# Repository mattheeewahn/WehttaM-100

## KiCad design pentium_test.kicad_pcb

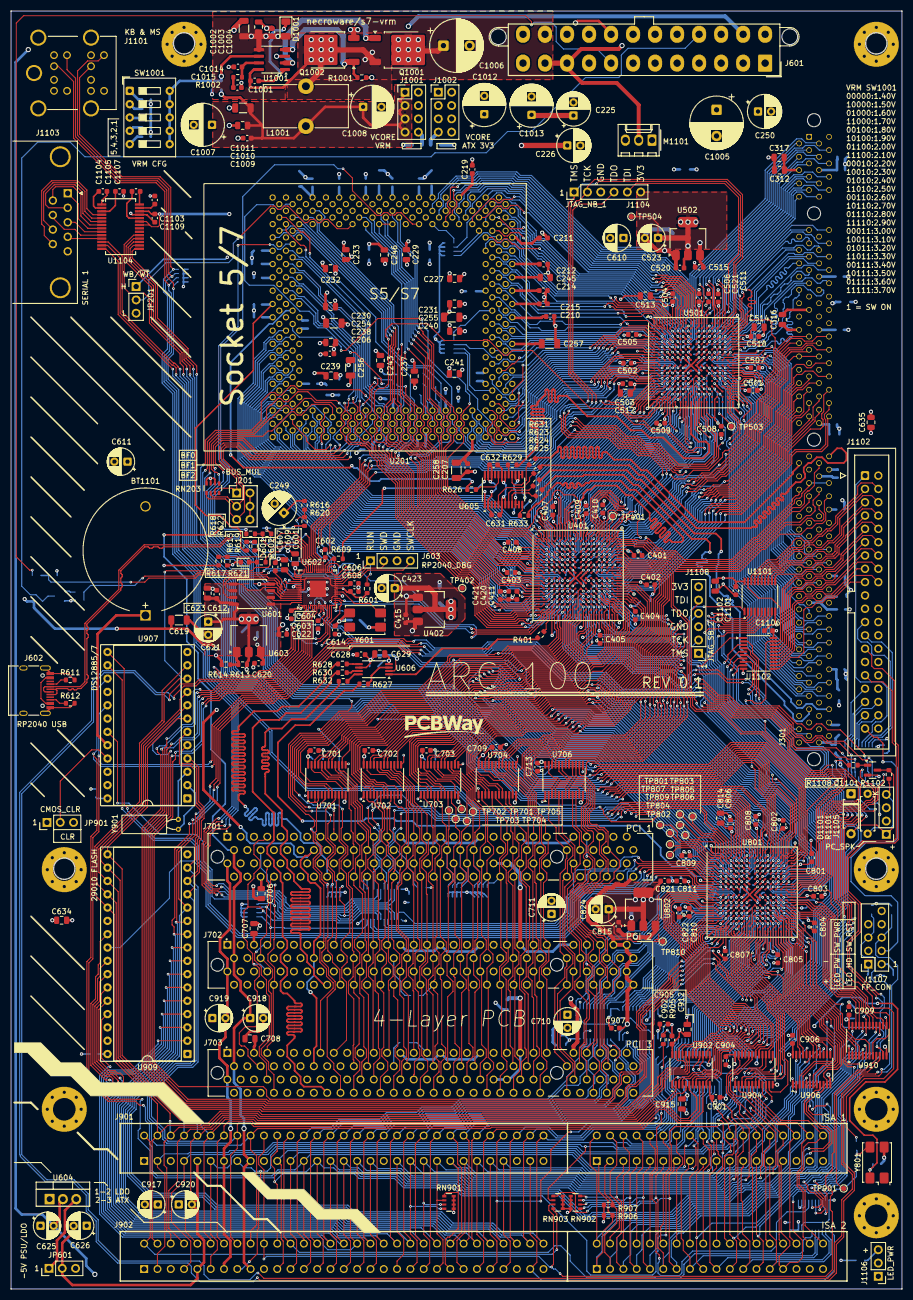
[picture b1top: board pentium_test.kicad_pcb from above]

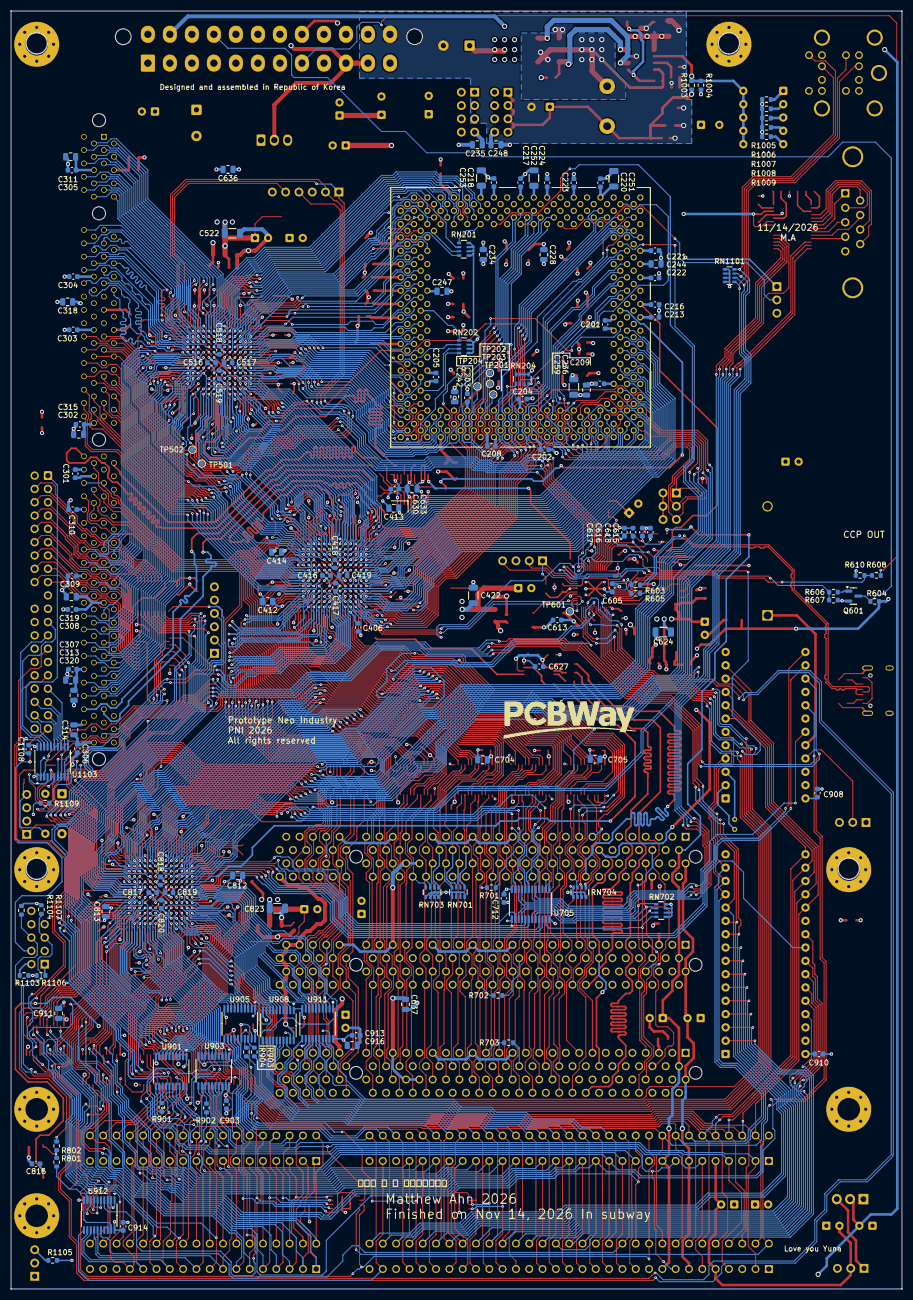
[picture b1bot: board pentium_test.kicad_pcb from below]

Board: 4 copper layers, 170.0 x 243.8 mm, 425 parts (143 on the bottom side), 774 nets.

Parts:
BT1101: Battery_Cell; BatteryHolder_MYOUNG_BS-07-A1BJ001_CR2032
C201, C202, C203, C204, C205, C206, C207, C208, C209, C210, C211, C212, C213, C214, C215, C216, C217, C218, C219, C220, C221, C222, C223, C224, C301, C302, C303, C304, C305, C306, C307, C308, C309, C310, C401, C402, C403, C404, C405, C406, C407, C408, C409, C410, C411, C415, C416, C417, C418, C419, C501, C502, C503, C504, C505, C506, C507, C508, C509, C510, C511, C515, C516, C517, C518, C519, C602, C603, C604, C605, C606, C607, C608, C612, C614, C615, C616, C617, C618, C620, C622, C627, C628, C630, C631, C632, C701, C702, C703, C709, C712, C713, C801, C802, C803, C804, C805, C806, C807, C808, C809, C810, C811, C815, C816, C817, C818, C819, C820, C901, C902, C903, C904, C905, C906, C907, C908, C909, C910, C913, C914, C1001, C1004, C1009, C1101, C1103, C1104, C1105, C1106, C1107, C1108, C1109: 100n; C_0603_1608Metric
C225, C226, C249, C250: 220u; CP_Radial_D6.3mm_P2.50mm
C227, C228, C229, C230, C231, C232, C233, C234, C235, C236, C237, C238, C239, C240, C241, C242, C243, C311, C312, C313, C314, C315, C316, C412, C413, C414, C512, C513, C514, C601, C609, C623, C629, C633, C634, C635, C636, C637, C704, C705, C706, C707, C708, C812, C813, C814, C911, C912, C915, C916, C1102: 1u; C_0805_2012Metric
C244, C245, C246, C247, C248, C317, C318, C319, C320, C1003, C1010: 4.7u; C_0805_2012Metric
C251, C252, C253, C254, C255, C422, C522, C619, C624, C823: 22u; C_1206_3216Metric
C256, C257, C258, C259, C1002, C1011: 10u; C_1206_3216Metric
C420, C421, C520, C521, C613, C821, C822: 4.7u; C_0603_1608Metric
C423, C523, C610, C611, C621, C710, C711, C824, C917, C918, C919, C920: 47u; CP_Radial_D5.0mm_P2.50mm
C625, C626: 22u; CP_Radial_D5.0mm_P2.50mm
C1005, C1006: 2200u; CP_Radial_D10.0mm_P5.00mm
C1007, C1008, C1012, C1013: 1000u; CP_Radial_D8.0mm_P3.50mm
C1014: 39p; C_0603_1608Metric
C1015: 242n; C_0603_1608Metric
D601: LED; LED_0603_1608Metric
D1001: D; D_1206_3216Metric
D1101: 1N4148; D_A-405_P7.62mm_Horizontal
H101, H102, H103, H104, H105, H106, H107: MountingHole_Pad; MountingHole_4.3mm_M4_Pad_Via
J201: Bus speed; PinHeader_2x03_P2.54mm_Vertical
J301: sdram
J601: ATX-24; Molex_Mini-Fit_Jr_5566-24A2_2x12_P4.20mm_Vertical
J602: USB_C_Receptacle_USB2.0_16P; USB_C_Receptacle_HRO_TYPE-C-31-M-12
J603: RP2040_DEBUG; PinHeader_1x04_P2.54mm_Vertical
J701, J702, J703: PCI 5V 32-bit; TE_1-5145154-2
J901, J902: TE_7-5530843-0
J1001, J1002: Conn_02x04_Odd_Even; PinHeader_2x04_P2.54mm_Vertical
J1101: MH11061-D2_kb_ms_combo
J1102: idc_02x20_IDE
J1103: RS232; DSUB-9_Pins_Horizontal_P2.77x2.84mm_EdgePinOffset7.70mm_Hou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
J1104: FPGA_JTAG1; PinHeader_1x06_P2.54mm_Vertical
J1105: PC_SPK; PinHeader_1x04_P2.54mm_Vertical
J1106: PWR_LED; PinHeader_1x03_P2.54mm_Vertical
J1107: front_panel_2x05
J1108: FPGA_JTAG2; PinHeader_1x06_P2.54mm_Vertical
JP201, JP601: Jumper_3_Open; PinHeader_1x03_P2.54mm_Vertical
JP901: CMOS_CLR; PinHeader_1x03_P2.54mm_Vertical
L1001: 3.3u; L_Toroid_Vertical_L16.0mm_W8.0mm_P7.62mm
M1101: Fan_PC_Chassis; Molex_KK-254_AE-6410-03A_1x03_P2.54mm_Vertical
Q601, Q1101: BSS138; SOT-23
Q1001, Q1002: Q_NMOS_GDS SM480T9RL; TO-252-2
R401, R609, R623, R624, R625, R626, R627, R628, R629, R630, R631, R632, R633, R801, R802, R901, R902, R903, R904, R905: 33; R_0603_1608Metric
R601, R602, R1102, R1103, R1105, R1106: 1K; R_0603_1608Metric
R603, R605: 27; R_0603_1608Metric
R604, R607, R616, R617, R622: 10K; R_0603_1608Metric
R606, R701, R702, R703, R1108: 100; R_0603_1608Metric
R608: 1.8K; R_0603_1608Metric
R610: 3.3K; R_0603_1608Metric
R611, R612: 5.1K; R_0603_1608Metric
R613: 120; R_0603_1608Metric
R614: 200; R_0603_1608Metric
R615, R1104, R1107, R1109: 4.7K; R_0603_1608Metric
R618, R620: 33K; R_0603_1608Metric
R619: 47K; R_0603_1608Metric
R621, R1001, R1002, R1006: 15K; R_0603_1608Metric
R906, R907: 300; R_0603_1608Metric
R1003: 5K; R_0603_1608Metric
R1004, R1008, R1009: 3.75K; R_0603_1608Metric
R1005: 30K; R_0603_1608Metric
R1007: 7.5K; R_0603_1608Metric
R1101: 47; R_Axial_DIN0207_L6.3mm_D2.5mm_P7.62mm_Horizontal
RN201, RN202, RN203, RN204, RN701, RN702, RN703, RN704, RN1101: 4.7K; R_Array_Convex_4x0603
RN901, RN902, RN903: 1K; R_Array_Convex_4x0603
SW1001: SW_DIP_x05; SW_DIP_SPSTx05_Slide_9.78x14.88mm_W7.62mm_P2.54mm
TP201: CPU_TMS; TestPoint_Pad_D1.0mm
TP202: CPU_TDO; TestPoint_Pad_D1.0mm
TP203: CPU_TDI; TestPoint_Pad_D1.0mm
TP204: CPU_TCK; TestPoint_Pad_D1.0mm
TP401, TP901: TestPoint; TestPoint_Pad_D1.0mm
TP402: CTRL_VCCINT; TestPoint_Pad_D1.0mm
TP501: FPGA_DATA_SPARE1; TestPoint_Pad_D1.0mm
TP502: FPGA_DATA_SPARE2; TestPoint_Pad_D1.0mm
TP503: FPGA_DATA_SPARE3; TestPoint_Pad_D1.0mm
TP504: DATA_VCCINT; TestPoint_Pad_D1.0mm
TP601: RP_GPIO12; TestPoint_Pad_D1.0mm
TP701: PCI_GND; TestPoint_Pad_D1.0mm
TP702: PCI5_FRAME; TestPoint_Pad_D1.0mm
TP703: PCI5_IRDY; TestPoint_Pad_D1.0mm
TP704: PCI5_TRDY; TestPoint_Pad_D1.0mm
TP705: PCI5_DEVSEL; TestPoint_Pad_D1.0mm
TP801: FPGA_ISA_SPARE1; TestPoint_Pad_D1.0mm
TP802: FPGA_ISA_SPARE6; TestPoint_Pad_D1.0mm
TP803: FPGA_ISA_SPARE2; TestPoint_Pad_D1.0mm
TP804: FPGA_ISA_SPARE7; TestPoint_Pad_D1.0mm
TP805: FPGA_ISA_SPARE3; TestPoint_Pad_D1.0mm
TP806: FPGA_ISA_SPARE8; TestPoint_Pad_D1.0mm
TP807: FPGA_ISA_SPARE4; TestPoint_Pad_D1.0mm
TP809: FPGA_ISA_SPARE5; TestPoint_Pad_D1.0mm
TP810: ISA_VCCINT; TestPoint_Pad_D1.0mm
U201: PGA321; PGA-321
U401, U501, U801: XC6SLX9-FTG256; Xilinx_FTG256
U402, U502, U802: LDL1117S12R; SOT-223-3_TabPin2
U601: W25Q128JVS; SOIC-8_5.3x5.3mm_P1.27mm
U602: RP2040; QFN-56-1EP_7x7mm_P0.4mm_EP3.2x3.2mm
U603: AMS1117; SOT-223-3_TabPin2
U604: LM7905_TO220; TO-220-3_Vertical
U605: CDCVF2310PW; TSSOP-24_4.4x7.8mm_P0.65mm
U606: CDCV304; TSSOP-8_4.4x3mm_P0.65mm
U701, U702, U703, U704, U705, U706, U902, U904, U906, U910: 74CBTD3384APW; TSSOP-24_4.4x7.8mm_P0.65mm
U901, U903, U905, U908, U911, U912, U1103: 74HCT541; TSSOP-20_4.4x6.5mm_P0.65mm
U907: DIP-24_W15.24mm_Socket
U909: SST39SF010; DIP-32_W15.24mm_Socket
U1001: ISL6545; SOIC-8_3.9x4.9mm_P1.27mm
U1101, U1102: SN74LVC245APW; TSSOP-20_4.4x6.5mm_P0.65mm
U1104: MAX3243E; SSOP-28_5.3x10.2mm_P0.65mm
Y601: 12 MHz; Crystal_SMD_7050-4Pin_7.0x5.0mm
Y801: 14.318 MHz; Crystal_SMD_7050-4Pin_7.0x5.0mm
Y901: 32.768 KHz; Crystal_C38-LF_D3.0mm_L8.0mm_Horizontal

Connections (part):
+1V2_F1: C416.1, C417.1, C418.1, C419.1, C420.1, C421.1, C422.1, C423.1, TP402.1, U401.G7 (VCCINT), U401.G9 (VCCINT), U401.H8 (VCCINT), U401.H10 (VCCINT), U401.J7 (VCCINT), U401.J9 (VCCINT), U401.K8 (VCCINT), U401.K10 (VCCINT), U402.2 (VO)
+1V2_F2: C516.1, C517.1, C518.1, C519.1, C520.1, C521.1, C522.1, C523.1, TP504.1, U501.G7 (VCCINT), U501.G9 (VCCINT), U501.H8 (VCCINT), U501.H10 (VCCINT), U501.J7 (VCCINT), U501.J9 (VCCINT), U501.K8 (VCCINT), U501.K10 (VCCINT), U502.2 (VO)
+1V2_F3: C817.1, C818.1, C819.1, C820.1, C821.1, C822.1, C823.1, C824.1, TP810.1, U801.G7 (VCCINT), U801.G9 (VCCINT), U801.H8 (VCCINT), U801.H10 (VCCINT), U801.J7 (VCCINT), U801.J9 (VCCINT), U801.K8 (VCCINT), U801.K10 (VCCINT), U802.2 (VO)
+3V3: C201.1, C202.1, C203.1, C204.1, C205.1, C206.1, C207.1, C208.1, C209.1, C210.1, C236.1, C237.1, C238.1, C239.1, C240.1, C241.1, C242.1, C243.1, C249.1, C250.1, C256.1, C257.1, C258.1, C259.1, C301.1, C302.1, C303.1, C304.1, C305.1, C306.1, C307.1, C308.1, C309.1, C310.1, C311.1, C312.1, C313.1, C314.1, C315.1, C316.1, C317.1, C318.1, C319.1, C320.1, C401.1, C402.1, C403.1, C404.1, C405.1, C406.1, C407.1, C408.1, C409.1, C410.1, C411.1, C412.1, C413.1, C414.1, C415.1, C501.1, C502.1, C503.1, C504.1, C505.1, C506.1, C507.1, C508.1, C509.1, C510.1, C511.1, C512.1, C513.1, C514.1, C515.1, C610.1, C627.1, C628.1, C629.1, C630.1, C631.1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
+3V3SB: C601.1, C602.1, C603.1, C604.1, C605.1, C606.1, C612.1, C613.1, C614.1, C621.1, C622.1, C623.1, C624.1, J701.A14 (3.3V_AUX), J702.A14 (3.3V_AUX), J703.A14 (3.3V_AUX), R601.1, R613.1, U601.8 (VCC), U602.1 (IOVDD), U602.10 (IOVDD), U602.22 (IOVDD), U602.33 (IOVDD), U602.42 (IOVDD), U602.43 (ADC_AVDD), U602.44 (VREG_IN), U602.48 (USB_VDD), U602.49 (IOVDD), U603.2 (VO), Y601.4 (Vdd)
+5V: C611.1, C634.1, C635.1, C701.1, C702.1, C703.1, C704.1, C705.1, C706.1, C707.1, C708.1, C709.1, C710.1, C712.1, C713.1, C901.2, C902.1, C903.2, C904.1, C905.2, C906.1, C907.2, C908.2, C909.1, C910.2, C911.1, C912.1, C913.2, C914.2, C915.1, C916.1, C917.1, C1002.1, C1003.1, C1004.1, C1005.1, C1006.1, C1108.2, D1001.2 (A), D1101.1 (K), J601.4 (+5V), J601.6 (+5V), J601.21 (+5V), J601.22 (+5V), J601.23 (+5V), J701.A5 (+5V), J701.A8 (+5V), J701.A10 (IOPWR), J701.A16 (IOPWR), J701.A59 (IOPWR), J701.A61 (+5V), J701.A62 (+5V), J701.B5 (+5V), J701.B6 (+5V), J701.B19 (IOPWR), J701.B59 (IOPWR), J701.B61 (+5V), J701.B62 (+5V), J702.A5 (+5V), J702.A8 (+5V), J702.A10 (IOPWR), J702.A16 (IOPWR), J702.A59 (IOPWR), J702.A61 (+5V), J702.A62 (+5V), J702.B5 (+5V), J702.B6 (+5V), J702.B19 (IOPWR), J702.B59 (IOPWR), J702.B61 (+5V), J702.B62 (+5V), J703.A5 (+5V), J703.A8 (+5V), J703.A10 (IOPWR), J703.A16 (IOPWR), J703.A59 (IOPWR), J703.A61 (+5V), J703.A62 (+5V), J703.B5 (+5V), J703.B6 (+5V)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
+5VSB: C619.1, C620.1, J601.9 (+5VSB), R604.1, U603.3 (VI)
+12V: C918.1, J601.10 (+12V), J601.11 (+12V), J701.A2 (+12V), J702.A2 (+12V), J703.A2 (+12V), J901.B9 (+12V), J902.B9 (+12V), M1101.2 (+), R618.1
+BATT: BT1101.1 (+), U907.20 (VBAT)
-5V: C626.2, C920.2, J901.B5 (-5V), J902.B5 (-5V), JP601.2 (C)
-5V_ATX: J601.20 (-5V), JP601.3 (B)
-12V: C625.2, C919.2, J601.14 (-12V), J701.B1 (-12V), J702.B1 (-12V), J703.B1 (-12V), J901.B7 (-12V), J902.B7 (-12V), U604.2 (VI)
/IO/IDE5_D0: J1102.17 (D0), U1102.11 (B8)
/IO/IDE5_D1: J1102.15 (D1), U1102.13 (B6)
/IO/IDE5_D2: J1102.13 (D2), U1102.15 (B4)
/IO/IDE5_D3: J1102.11 (D3), U1102.17 (B2)
/IO/IDE5_D4: J1102.9 (D4), U1101.11 (B8)
/IO/IDE5_D5: J1102.7 (D5), U1101.13 (B6)
/IO/IDE5_D6: J1102.5 (D6), U1101.15 (B4)
/IO/IDE5_D7: J1102.3 (D7), U1101.17 (B2)
/IO/IDE5_D8: J1102.4 (D8), U1101.18 (B1)
/IO/IDE5_D9: J1102.6 (D9), U1101.16 (B3)
/IO/IDE5_D10: J1102.8 (D10), U1101.14 (B5)
/IO/IDE5_D11: J1102.10 (D11), U1101.12 (B7)
/IO/IDE5_D12: J1102.12 (D12), U1102.18 (B1)
/IO/IDE5_D13: J1102.14 (D13), U1102.16 (B3)
/IO/IDE5_D14: J1102.16 (D14), U1102.14 (B5)
/IO/IDE5_D15: J1102.18 (D15), U1102.12 (B7)
/IO/IDE5_DASP: J1102.39 (~DASP), J1107.3
/IO/IDE_BUF_DA0: J1102.35 (DA0), U1103.12 (Y6)
/IO/IDE_BUF_DA1: J1102.33 (DA1), U1103.11 (Y7)
/IO/IDE_BUF_DA2: J1102.36 (DA2), U1103.13 (Y5)
/IO/RS232_1_CTS: J1103.8, U1104.5 (RIN2)
/IO/RS232_1_DCD: J1103.1, U1104.8 (RIN5)
/IO/RS232_1_DSR: J1103.6, U1104.7 (RIN4)
/IO/RS232_1_DTR: J1103.4, U1104.11 (DOUT3)
/IO/RS232_1_RI: J1103.9, U1104.4 (RIN1)
/IO/RS232_1_RTS: J1103.7, U1104.10 (DOUT2)
/IO/RS232_1_RXD: J1103.2, U1104.6 (RIN3)
/IO/RS232_1_TXD: J1103.3, U1104.9 (DOUT1)
/IO/~IDE_BUF_CS1FX: J1102.37 (~CS1FX), U1103.14 (Y4)
/IO/~IDE_BUF_CS3FX: J1102.38 (~CS3FX), U1103.15 (Y3)
/IO/~IDE_BUF_DIOR: J1102.25 (~DIOR), U1103.18 (Y0)
/IO/~IDE_BUF_DIOW: J1102.23 (~DIOW), U1103.17 (Y1)
/IO/~IDE_BUF_RESET: J1102.1 (~RESET), U1103.16 (Y2)
/ISA/ISA5_AEN: J901.A11 (AEN), J902.A11 (AEN), U901.11 (Y7)
/ISA/ISA5_ALE: J901.B28 (ALE), J902.B28 (ALE), U903.11 (Y7)
/ISA/ISA5_CLK: J901.B20 (CLK), J902.B20 (CLK), U901.15 (Y3)
/ISA/ISA5_DRQ0: J901.D9 (DRQ0), J902.D9 (DRQ0), U910.5 (1B2)
/ISA/ISA5_DRQ1: J901.B18 (DRQ1), J902.B18 (DRQ1), U906.16 (2B2)
/ISA/ISA5_DRQ2: J901.B6 (DRQ2), J902.B6 (DRQ2), U904.15 (2B1)
/ISA/ISA5_DRQ3: J901.B16 (DRQ3), J902.B16 (DRQ3), U906.5 (1B2)
/ISA/ISA5_DRQ5: J901.D11 (DRQ5), J902.D11 (DRQ5), U910.6 (1B3)
/ISA/ISA5_DRQ6: J901.D13 (DRQ6), J902.D13 (DRQ6), U910.16 (2B2)
/ISA/ISA5_DRQ7: J901.D15 (DRQ7), J902.D15 (DRQ7), U910.15 (2B1)
/ISA/ISA5_IRQ2: J901.B4 (IRQ2), J902.B4 (IRQ2), RN903.2 (R2.1), U904.16 (2B2)
/ISA/ISA5_IRQ3: J901.B25 (IRQ3), J902.B25 (IRQ3), U904.10 (1B5)
/ISA/ISA5_IRQ4: J901.B24 (IRQ4), J902.B24 (IRQ4), RN901.1 (R1.1), U906.23 (2B5)
/ISA/ISA5_IRQ5: J901.B23 (IRQ5), J902.B23 (IRQ5), RN901.2 (R2.1), U906.20 (2B4)
/ISA/ISA5_IRQ6: J901.B22 (IRQ6), J902.B22 (IRQ6), RN901.3 (R3.1), U906.2 (1B1)
/ISA/ISA5_IRQ7: J901.B21 (IRQ7), J902.B21 (IRQ7), RN901.4 (R4.1), U906.19 (2B3)
/ISA/ISA5_IRQ10: J901.D3 (IRQ10), J902.D3 (IRQ10), RN902.4 (R4.1), U906.10 (1B5)
/ISA/ISA5_IRQ11: J901.D4 (IRQ11), J902.D4 (IRQ11), RN902.3 (R3.1), U910.23 (2B5)
/ISA/ISA5_IRQ12: J901.D5 (IRQ12), J902.D5 (IRQ12), RN902.2 (R2.1), U910.2 (1B1)
/ISA/ISA5_IRQ15: J901.D6 (IRQ15), J902.D6 (IRQ15), RN902.1 (R1.1), U910.20 (2B4)
/ISA/ISA5_LA17: J901.C8 (LA17), J902.C8 (LA17), U903.16 (Y2)
/ISA/ISA5_LA18: J901.C7 (LA18), J902.C7 (LA18), U905.11 (Y7)
/ISA/ISA5_LA19: J901.C6 (LA19), J902.C6 (LA19), U905.14 (Y4)
/ISA/ISA5_LA20: J901.C5 (LA20), J902.C5 (LA20), U905.15 (Y3)
/ISA/ISA5_LA21: J901.C4 (LA21), J902.C4 (LA21), U905.13 (Y5)
/ISA/ISA5_LA22: J901.C3 (LA22), J902.C3 (LA22), U905.12 (Y6)
/ISA/ISA5_LA23: J901.C2 (LA23), J902.C2 (LA23), U903.18 (Y0)
/ISA/ISA5_OSC: J901.B30 (OSC), J902.B30 (OSC), U912.11 (Y7)
/ISA/ISA5_RESET: J901.B2 (RESET), J902.B2 (RESET), U903.17 (Y1)
/ISA/ISA5_SBHE: J901.C1 (SBHE), J902.C1 (SBHE), U906.6 (1B3)
/ISA/ISA5_TC: J901.B27 (TC), J902.B27 (TC), U901.17 (Y1)
/ISA/SB_SPARE5_1: TP901.1, U910.10 (1B5)
/ISA/~CMOS_CLR: JP901.2 (C), U907.21 (~RCLR)
/ISA/~ISA5_DACK0: J901.D8 (~DACK0), J902.D8 (~DACK0), U912.15 (Y3)
/ISA/~ISA5_DACK1: J901.B17 (~DACK1), J902.B17 (~DACK1), U901.14 (Y4)
/ISA/~ISA5_DACK2: J901.B26 (~DACK2), J902.B26 (~DACK2), U901.16 (Y2)
/ISA/~ISA5_DACK3: J901.B15 (~DACK3), J902.B15 (~DACK3), U901.13 (Y5)
/ISA/~ISA5_DACK5: J901.D10 (~DACK5), J902.D10 (~DACK5), U912.14 (Y4)
/ISA/~ISA5_DACK6: J901.D12 (~DACK6), J902.D12 (~DACK6), U912.13 (Y5)
/ISA/~ISA5_DACK7: J901.D14 (~DACK7), J902.D14 (~DACK7), U912.12 (Y6)
/ISA/~ISA5_IOCHECK: J901.A1 (IO), J902.A1 (IO), RN903.4 (R4.1)
/ISA/~ISA5_IOCS16: J901.D2 (~IOCS16), J902.D2 (~IOCS16), R907.1, U906.9 (1B4)
/ISA/~ISA5_MEMCS16: J901.D1 (~MEMCS16), J902.D1 (~MEMCS16), R906.1, U906.15 (2B1)
/ISA/~ISA5_MEMR: J901.C9 (~MEMR), J902.C9 (~MEMR), U903.13 (Y5)
/ISA/~ISA5_MEMW: J901.C10 (~MEMW), J902.C10 (~MEMW), U901.18 (Y0)
/ISA/~ISA5_NOWS: J901.B8 (~NOWS), J902.B8 (~NOWS), U904.9 (1B4)
/ISA/~ISA5_SMEMR: J901.B12 (~SMEMR), J902.B12 (~SMEMR), U903.14 (Y4)
/ISA/~ISA5_SMEMW: J901.B11 (~SMEMW), J902.B11 (~SMEMW), U903.15 (Y3)
/PCI/PCI5_PAR: J701.A43 (PAR), J702.A43 (PAR), J703.A43 (PAR), U704.5 (1B2)
/PCI/PCI_S1_IDSEL: J701.A26 (IDSEL), R701.1
/PCI/PCI_S2_IDSEL: J702.A26 (IDSEL), R702.2
/PCI/PCI_S3_IDSEL: J703.A26 (IDSEL), R703.2
/PCI/~PCI5_CBE0: J701.A52 (C/BE0#), J702.A52 (C/BE0#), J703.A52 (C/BE0#), U706.2 (1B1)
/PCI/~PCI5_CBE1: J701.B44 (C/BE1#), J702.B44 (C/BE1#), J703.B44 (C/BE1#), U704.9 (1B4)
/PCI/~PCI5_CBE2: J701.B33 (C/BE2#), J702.B33 (C/BE2#), J703.B33 (C/BE2#), U703.6 (1B3)
/PCI/~PCI5_CBE3: J701.B26 (C/BE3#), J702.B26 (C/BE3#), J703.B26 (C/BE3#), U702.9 (1B4)
/PCI/~PCI5_DEVSEL: J701.B37 (DEVSEL#), J702.B37 (DEVSEL#), J703.B37 (DEVSEL#), RN701.4 (R4.1), TP705.1, U703.20 (2B4)
/PCI/~PCI5_FRAME: J701.A34 (FRAME#), J702.A34 (FRAME#), J703.A34 (FRAME#), RN701.1 (R1.1), TP702.1, U703.9 (1B4)
/PCI/~PCI5_INT1: J701.A6 (INTA#), J702.B8 (INTD#), J703.A7 (INTC#), RN702.1 (R1.1), U705.4 (1A2)
/PCI/~PCI5_INT2: J701.B7 (INTB#), J702.A6 (INTA#), J703.B8 (INTD#), RN702.2 (R2.1), U705.7 (1A3)
/PCI/~PCI5_INT3: J701.A7 (INTC#), J702.B7 (INTB#), J703.A6 (INTA#), RN702.3 (R3.1), U705.8 (1A4)
/PCI/~PCI5_INT4: J701.B8 (INTD#), J702.A7 (INTC#), J703.B7 (INTB#), RN702.4 (R4.1), U705.11 (1A5)
/PCI/~PCI5_IRDY: J701.B35 (IRDY#), J702.B35 (IRDY#), J703.B35 (IRDY#), RN701.2 (R2.1), TP703.1, U703.10 (1B5)
/PCI/~PCI5_LOCK: J701.B39 (LOCK#), J702.B39 (LOCK#), J703.B39 (LOCK#), RN703.2 (R2.1), U703.16 (2B2)
/PCI/~PCI5_PERR: J701.B40 (PERR#), J702.B40 (PERR#), J703.B40 (PERR#), RN703.3 (R3.1), U703.15 (2B1)
/PCI/~PCI5_S1_REQ: J701.B18 (REQ#), RN704.3 (R3.1), U701.10 (1B5)
/PCI/~PCI5_S2_REQ: J702.B18 (REQ#), RN704.2 (R2.1), U701.9 (1B4)
/PCI/~PCI5_S3_REQ: J703.B18 (REQ#), RN704.1 (R1.1), U701.6 (1B3)
/PCI/~PCI5_SERR: J701.B42 (SERR#), J702.B42 (SERR#), J703.B42 (SERR#), RN703.4 (R4.1), U704.2 (1B1)
/PCI/~PCI5_STOP: J701.A38 (STOP#), J702.A38 (STOP#), J703.A38 (STOP#), RN703.1 (R1.1), U703.19 (2B3)
/PCI/~PCI5_TRDY: J701.A36 (TRDY#), J702.A36 (TRDY#), J703.A36 (TRDY#), RN701.3 (R3.1), TP704.1, U703.23 (2B5)
/cpu_pentium/AP: RN204.4 (R4.1), U201.AK02 (AP)
/cpu_pentium/WB/~WT: JP201.2 (C), U201.AA05 (WB/WT#)
/cpu_pentium/~FRCMC: RN204.2 (R2.1), U201.Y35 (FRCMC#1)
/cpu_pentium/~PEN: RN204.3 (R3.1), U201.Z34 (PEN#)
/cpu_pentium/~TRST: RN204.1 (R1.1), U201.Q33 (TRST#)
/fpga_data/FPGA_DATA_SPARE1: TP501.1, U501.K11 (IO_L42N_GCLK6_TRDY1_M1LDM_1)
/fpga_data/FPGA_DATA_SPARE2: TP502.1, U501.P11 (IO_L13N_D10_2)
/fpga_data/FPGA_DATA_SPARE3: TP503.1, U501.N12 (IO_L12P_D1_MISO2_2)
/fpga_isa/FPGA_ISA_SPARE1: TP801.1, U801.B3 (IO_L83P_3)
/fpga_isa/FPGA_ISA_SPARE2: TP803.1, U801.A3 (IO_L83N_VREF_3)
/fpga_isa/FPGA_ISA_SPARE3: TP805.1, U801.A2 (IO_L52N_M3A9_3)
/fpga_isa/FPGA_ISA_SPARE4: TP807.1, U801.B2 (IO_L52P_M3A8_3)
/fpga_isa/FPGA_ISA_SPARE5: TP809.1, U801.B1 (IO_L50N_M3BA2_3)
/fpga_isa/FPGA_ISA_SPARE6: TP802.1, U801.C1 (IO_L50P_M3WE_3)
/fpga_isa/FPGA_ISA_SPARE7: TP804.1, U801.C2 (IO_L48N_M3BA1_3)
/fpga_isa/FPGA_ISA_SPARE8: TP806.1, U801.C3 (IO_L48P_M3BA0_3)
/fpga_isa/ISA_FPGA_OSC: R802.2, U801.J16 (IO_L43N_GCLK4_M1DQ5_1)
/power_syscon/ADC_3V3: C617.1, R616.2, R620.1, U602.39 (GPIO27_ADC1)
/power_syscon/ADC_5V: C616.1, R617.2, R621.1, U602.40 (GPIO28_ADC2)
/power_syscon/ADC_12V: C615.1, R618.2, R622.1, U602.41 (GPIO29_ADC3)
/power_syscon/ADC_VCORE: C618.1, R615.2, R619.1, U602.38 (GPIO26_ADC0)
/power_syscon/MAIN_CLK66: R609.2, U605.24 (CLK)
/power_syscon/PWR_OK: J601.8 (PWR_OK), R608.1
/power_syscon/RP2040_D+: J602.A6 (D+), J602.B6 (D+), R603.1
/power_syscon/RP2040_D-: J602.A7 (D-), J602.B7 (D-), R605.1
/power_syscon/RP2040_LED: R602.1, U602.37 (GPIO25)
/power_syscon/RP2040_RUN: J603.1, R601.2, U602.26 (RUN)
/power_syscon/RP2040_SWCLK: J603.4, U602.24 (SWCLK)
/power_syscon/RP2040_SWD: J603.2, U602.25 (SWD)
/power_syscon/RPI_QSPI_SCLK: U601.6 (CLK), U602.52 (QSPI_SCLK)
/power_syscon/RPI_QSPI_SD0: U601.5 (DI/IO_{0}), U602.53 (QSPI_SD0)
/power_syscon/RPI_QSPI_SD1: U601.2 (DO/IO_{1}), U602.55 (QSPI_SD1)
/power_syscon/RPI_QSPI_SD2: U601.3 (~WP/IO_{2}), U602.54 (QSPI_SD2)
/power_syscon/RPI_QSPI_SD3: U601.7 (~HOLD/~RESET/IO_{3}), U602.51 (QSPI_SD3)
/power_syscon/RPI_QSPI_SS: U601.1 (~CS), U602.56 (QSPI_SS)
/power_syscon/RP_PS_ON: R606.1, R607.1, U602.28 (GPIO17)
/power_syscon/RP_PWR_OK: R608.2, R610.1, U602.27 (GPIO16)
/power_syscon/USBC_VBUS_UNUSED: J602.A4 (VBUS), J602.A9 (VBUS), J602.B4 (VBUS), J602.B9 (VBUS)
/power_syscon/~PS_ON: J601.16 (PS_ON#), Q601.3 (D), R604.2
/vrms/VCORE_BG: Q1002.1 (G), R1001.2, U1001.4 (BG)
/vrms/VCORE_COMP: C1014.1, R1002.1, U1001.7 (COMP/~DIS)
/vrms/VCORE_FB: R1003.2, R1004.1, SW1001.6, SW1001.7, SW1001.8, SW1001.9, SW1001.10, U1001.6 (FB)
/vrms/VCORE_PHASE: C1001.2, L1001.1, Q1001.3 (S), Q1002.2 (D), U1001.8 (PHASE)
/vrms/VCORE_REG_OUT: C1007.1, C1008.1, C1009.1, C1010.1, C1011.1, J1001.1, J1001.3, J1001.5, J1001.7, L1001.2, R1003.1
/vrms/VCORE_TG: Q1001.1 (G), U1001.2 (TG)
A20M#: U201.AK08 (A20M#), U801.C16 (IO_L33N_A14_M1A4_1)
AHOLD: U201.V04 (AHOLD), U401.C2 (IO_L48N_M3BA1_3)
BTN_PWR: J1107.6, R1107.1, U602.14 (GPIO11)
BTN_RESET: J1107.5, R1104.1, U602.13 (GPIO10)
CPU_CLK: R626.2, U201.AK18 (CLK)
CPU_RESET: U201.AK20 (RESET), U401.B8 (IO_L33P_0)
C_A3: U201.AL35 (A3), U401.H3 (IO_L44N_GCLK20_M3A6_3)
C_A4: U201.AM34 (A4), U401.K6 (IO_L47N_M3A1_3)
C_A5: U201.AK32 (A5), U401.J6 (IO_L43P_GCLK23_M3RASN_3)
C_A6: U201.AN33 (A6), U401.J3 (IO_L38P_M3DQ2_3)
C_A7: U201.AL33 (A7), U401.K5 (IO_L47P_M3A0_3)
C_A8: U201.AM32 (A8), U401.K3 (IO_L42P_GCLK25_TRDY2_M3UDM_3)
C_A9: U201.AK30 (A9), U401.L8 (IO_L62P_D5_2)
C_A10: U201.AN31 (A10), U401.L3 (IO_L36P_M3DQ8_3)
C_A11: U201.AL31 (A11), U401.J4 (IO_L42N_GCLK24_M3LDM_3)
C_A12: U201.AL29 (A12), U401.M1 (IO_L35N_M3DQ11_3)
C_A13: U201.AK28 (A13), U401.L4 (IO_L45P_M3A3_3)
C_A14: U201.AL27 (A14), U401.L5 (IO_L45N_M3ODT_3)
C_A15: U201.AK26 (A15), U401.M3 (IO_L1N_VREF_3)
C_A16: U201.AL25 (A16), U401.M4 (IO_L1P_3)
C_A17: U201.AK24 (A17), U401.N4 (IO_L2N_3)
C_A18: U201.AL23 (A18), U401.N1 (IO_L34N_M3UDQSN_3)
C_A19: U201.AK22 (A19), U401.N3 (IO_L34P_M3UDQS_3)
C_A20: U201.AL21 (A20), U401.P1 (IO_L33N_M3DQ13_3)
C_A21: U201.AF34 (A21), U401.F5 (IO_L55N_M3A14_3)
C_A22: U201.AH36 (A22), U401.F3 (IO_L53N_M3A12_3)
C_A23: U201.AE33 (A23), U401.D3 (IO_L49P_M3A7_3)
C_A24: U201.AG35 (A24), U401.F4 (IO_L53P_M3CKE_3)
C_A25: U201.AJ35 (A25), U401.G3 (IO_L40P_M3DQ6_3)
C_A26: U201.AH34 (A26), U401.G5 (IO_L51N_M3A4_3)
C_A27: U201.AG33 (A27), U401.E3 (IO_L54N_M3A11_3)
C_A28: U201.AK36 (A28), U401.H4 (IO_L44P_GCLK21_M3A5_3)
C_A29: U201.AK34 (A29), U401.G6 (IO_L51P_M3A10_3)
C_A30: U201.AM36 (A30), U401.H5 (IO_L43N_GCLK22_IRDY2_M3CASN_3)
C_A31: U201.AJ33 (A31), U401.E4 (IO_L54P_M3RESET_3)
C_D0: U201.K34 (D0), U501.M1 (IO_L35N_M3DQ11_3)
C_D1: U201.G35 (D1), U501.M2 (IO_L35P_M3DQ10_3)
C_D2: U201.J35 (D2), U501.L1 (IO_L36N_M3DQ9_3)
C_D3: U201.G33 (D3), U501.K1 (IO_L37N_M3DQ1_3)
C_D4: U201.F36 (D4), U501.K2 (IO_L37P_M3DQ0_3)
C_D5: U201.F34 (D5), U501.J1 (IO_L38N_M3DQ3_3)
C_D6: U201.E35 (D6), U501.H1 (IO_L39N_M3LDQSN_3)
C_D7: U201.E33 (D7), U501.H2 (IO_L39P_M3LDQS_3)
C_D8: U201.D34 (D8), U501.L5 (IO_L45N_M3ODT_3)
C_D9: U201.C37 (D9), U501.K3 (IO_L42P_GCLK25_TRDY2_M3UDM_3)
C_D10: U201.C35 (D10), U501.J4 (IO_L42N_GCLK24_M3LDM_3)
C_D11: U201.B36 (D11), U501.J3 (IO_L38P_M3DQ2_3)
C_D12: U201.D32 (D12), U501.K5 (IO_L47P_M3A0_3)
C_D13: U201.B34 (D13), U501.K6 (IO_L47N_M3A1_3)
C_D14: U201.C33 (D14), U501.J6 (IO_L43P_GCLK23_M3RASN_3)
C_D15: U201.A35 (D15), U501.H5 (IO_L43N_GCLK22_IRDY2_M3CASN_3)
C_D16: U201.B32 (D16), U501.G1 (IO_L40N_M3DQ7_3)
C_D17: U201.C31 (D17), U501.F1 (IO_L41N_GCLK26_M3DQ5_3)
C_D18: U201.A33 (D18), U501.F2 (IO_L41P_GCLK27_M3DQ4_3)
C_D19: U201.D28 (D19), U501.E1 (IO_L46N_M3CLKN_3)
C_D20: U201.B30 (D20), U501.E2 (IO_L46P_M3CLK_3)
C_D21: U201.C29 (D21), U501.D1 (IO_L49N_M3A2_3)
C_D22: U201.A31 (D22), U501.C1 (IO_L50P_M3WE_3)
C_D23: U201.D26 (D23), U501.C2 (IO_L48N_M3BA1_3)
C_D24: U201.C27 (D24), U501.H3 (IO_L44N_GCLK20_M3A6_3)
C_D25: U201.C23 (D25), U501.G3 (IO_L40P_M3DQ6_3)
C_D26: U201.D24 (D26), U501.H4 (IO_L44P_GCLK21_M3A5_3)
C_D27: U201.C21 (D27), U501.F3 (IO_L53N_M3A12_3)
C_D28: U201.D22 (D28), U501.G5 (IO_L51N_M3A4_3)
C_D29: U201.C19 (D29), U501.E3 (IO_L54N_M3A11_3)
C_D30: U201.D20 (D30), U501.F4 (IO_L53P_M3CKE_3)
C_D31: U201.C17 (D31), U501.F5 (IO_L55N_M3A14_3)
C_D32: U201.C15 (D32), U501.B1 (IO_L50N_M3BA2_3)
C_D33: U201.D16 (D33), U501.B2 (IO_L52P_M3A8_3)
C_D34: U201.C13 (D34), U501.C3 (IO_L48P_M3BA0_3)
C_D35: U201.D14 (D35), U501.A2 (IO_L52N_M3A9_3)
C_D36: U201.C11 (D36), U501.B3 (IO_L83P_3)
C_D37: U201.D12 (D37), U501.A3 (IO_L83N_VREF_3)
C_D38: U201.C09 (D38), U501.C4 (IO_L1P_HSWAPEN_0)
C_D39: U201.D10 (D39), U501.A4 (IO_L1N_VREF_0)
C_D40: U201.D08 (D40), U501.D3 (IO_L49P_M3A7_3)
C_D41: U201.A05 (D41), U501.E6 (IO_L5N_0)
C_D42: U201.E09 (D42), U501.E4 (IO_L54P_M3RESET_3)
C_D43: U201.B04 (D43), U501.C5 (IO_L3N_0)
C_D44: U201.D06 (D44), U501.D5 (IO_L3P_0)
C_D45: U201.C05 (D45), U501.G6 (IO_L51P_M3A10_3)
C_D46: U201.E07 (D46), U501.D6 (IO_L7P_0)
C_D47: U201.C03 (D47), U501.C6 (IO_L7N_0)
C_D48: U201.D04 (D48), U501.A5 (IO_L2N_0)
C_D49: U201.E05 (D49), U501.B5 (IO_L2P_0)
C_D50: U201.D02 (D50), U501.A6 (IO_L4N_0)
C_D51: U201.F04 (D51), U501.B6 (IO_L4P_0)
C_D52: U201.E03 (D52), U501.A7 (IO_L6N_0)
C_D53: U201.G05 (D53), U501.A8 (IO_L33N_0)
C_D54: U201.E01 (D54), U501.B8 (IO_L33P_0)
C_D55: U201.G03 (D55), U501.A9 (IO_L34N_GCLK18_0)
C_D56: U201.H04 (D56), U501.F6 (IO_L55P_M3A13_3)
C_D57: U201.J03 (D57), U501.C7 (IO_L6P_0)
C_D58: U201.J05 (D58), U501.D8 (IO_L38P_0)
C_D59: U201.K04 (D59), U501.C8 (IO_L38N_VREF_0)
C_D60: U201.L05 (D60), U501.E7 (IO_L36P_GCLK15_0)
C_D61: U201.L03 (D61), U501.E8 (IO_L36N_GCLK14_0)
C_D62: U201.M04 (D62), U501.F7 (IO_L5P_0)
C_D63: U201.N03 (D63), U501.F9 (IO_L40P_0)
FPGA_CTRL_CCLK: J701.A17 (GNT#), U401.R11 (IO_L1P_CCLK_2), U602.8 (GPIO6)
FPGA_CTRL_CLK: R633.2, U401.A9 (IO_L34N_GCLK18_0)
FPGA_CTRL_DIN: U401.P10 (IO_L3P_D0_DIN_MISO_MISO1_2), U602.9 (GPIO7)
FPGA_CTRL_DONE: U401.P13 (DONE_2), U602.16 (GPIO13)
FPGA_CTRL_INIT: U401.R3 (IO_L65P_INIT_B_2), U602.17 (GPIO14)
FPGA_CTRL_PROGRAM: U401.T2 (PROGRAM_B_2), U602.18 (GPIO15)
FPGA_DATA_CCLK: U501.R11 (IO_L1P_CCLK_2), U602.29 (GPIO18)
FPGA_DATA_CLK: R629.2, U501.T8 (IO_L30N_GCLK0_USERCCLK_2)
FPGA_DATA_DIN: U501.P10 (IO_L3P_D0_DIN_MISO_MISO1_2), U602.30 (GPIO19)
FPGA_DATA_DONE: U501.P13 (DONE_2), U602.34 (GPIO22)
FPGA_DATA_INIT: U501.R3 (IO_L65P_INIT_B_2), U602.35 (GPIO23)
FPGA_DATA_PROGRAM: U501.T2 (PROGRAM_B_2), U602.36 (GPIO24)
FPGA_ISA_CCLK: U602.4 (GPIO2), U801.R11 (IO_L1P_CCLK_2)
FPGA_ISA_DIN: U602.5 (GPIO3), U801.P10 (IO_L3P_D0_DIN_MISO_MISO1_2)
FPGA_ISA_DONE: U602.3 (GPIO1), U801.P13 (DONE_2)
FPGA_ISA_INIT: U602.6 (GPIO4), U801.R3 (IO_L65P_INIT_B_2)
FPGA_ISA_PROGRAM: U602.7 (GPIO5), U801.T2 (PROGRAM_B_2)
GND: BT1101.2 (-), C201.2, C202.2, C203.2, C204.2, C205.2, C206.2, C207.2, C208.2, C209.2, C210.2, C211.2, C212.2, C213.2, C214.2, C215.2, C216.2, C217.2, C218.2, C219.2, C220.2, C221.2, C222.2, C223.2, C224.2, C225.2, C226.2, C227.2, C228.2, C229.2, C230.2, C231.2, C232.2, C233.2, C234.2, C235.2, C236.2, C237.2, C238.2, C239.2, C240.2, C241.2, C242.2, C243.2, C244.2, C245.2, C246.2, C247.2, C248.2, C249.2, C250.2, C251.2, C252.2, C253.2, C254.2, C255.2, C256.2, C257.2, C258.2, C259.2, C301.2, C302.2, C303.2, C304.2, C305.2, C306.2, C307.2, C308.2, C309.2, C310.2, C311.2, C312.2, C313.2, C314.2, C315.2, C316.2, C317.2, C318.2, C319.2, C320.2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
IBUS_CMD0: U401.A11 (IO_L39N_0), U501.L10 (IO_L16P_2)
IBUS_CMD1: U401.A12 (IO_L62N_VREF_0), U501.M9 (IO_L29P_GCLK3_2)
IBUS_CMD2: U401.B12 (IO_L62P_0), U501.R9 (IO_L23P_2)
IBUS_CMD3: U401.A13 (IO_L63N_SCP6_0), U501.N9 (IO_L14P_D11_2)
IBUS_CMD4: U401.A14 (IO_L65N_SCP2_0), U501.T9 (IO_L23N_2)
IBUS_D0: U401.C3 (IO_L48P_M3BA0_3), U501.L3 (IO_L36P_M3DQ8_3)
IBUS_D1: U401.A2 (IO_L52N_M3A9_3), U501.L4 (IO_L45P_M3A3_3)
IBUS_D2: U401.B3 (IO_L83P_3), U501.M3 (IO_L1N_VREF_3)
IBUS_D3: U401.A3 (IO_L83N_VREF_3), U501.L8 (IO_L62P_D5_2)
IBUS_D4: U401.C4 (IO_L1P_HSWAPEN_0), U501.M4 (IO_L1P_3)
IBUS_D5: U401.A4 (IO_L1N_VREF_0), U501.N4 (IO_L2N_3)
IBUS_D6: U401.E6 (IO_L5N_0), U501.N1 (IO_L34N_M3UDQSN_3)
IBUS_D7: U401.D5 (IO_L3P_0), U501.N3 (IO_L34P_M3UDQS_3)
IBUS_D8: U401.C5 (IO_L3N_0), U501.P1 (IO_L33N_M3DQ13_3)
IBUS_D9: U401.A5 (IO_L2N_0), U501.P2 (IO_L33P_M3DQ12_3)
IBUS_D10: U401.B5 (IO_L2P_0), U501.R1 (IO_L32N_M3DQ15_3)
IBUS_D11: U401.D6 (IO_L7P_0), U501.R2 (IO_L32P_M3DQ14_3)
IBUS_D12: U401.C6 (IO_L7N_0), U501.P9 (IO_L14N_D12_2)
IBUS_D13: U401.F6 (IO_L55P_M3A13_3), U501.M5 (IO_L2P_3)
IBUS_D14: U401.C7 (IO_L6P_0), U501.N5 (IO_L49P_D3_2)
IBUS_D15: U401.D8 (IO_L38P_0), U501.P5 (IO_L49N_D4_2)
IBUS_D16: U401.C8 (IO_L38N_VREF_0), U501.P4 (IO_L63P_2)
IBUS_D17: U401.A6 (IO_L4N_0), U501.T3 (IO_L65N_CSO_B_2)
IBUS_D18: U401.B6 (IO_L4P_0), U501.N6 (IO_L64N_D9_2)
IBUS_D19: U401.A7 (IO_L6N_0), U501.P6 (IO_L47P_2)
IBUS_D20: U401.A8 (IO_L33N_0), U501.R5 (IO_L48P_D7_2)
IBUS_D21: U401.E7 (IO_L36P_GCLK15_0), U501.T5 (IO_L48N_RDWR_B_VREF_2)
IBUS_D22: U401.E8 (IO_L36N_GCLK14_0), U501.M6 (IO_L64P_D8_2)
IBUS_D23: U401.F7 (IO_L5P_0), U501.T4 (IO_L63N_2)
IBUS_D24: U401.F9 (IO_L40P_0), U501.T6 (IO_L47N_2)
IBUS_D25: U401.C9 (IO_L34P_GCLK19_0), U501.R7 (IO_L32P_GCLK29_2)
IBUS_D26: U401.A10 (IO_L35N_GCLK16_0), U501.P7 (IO_L31P_GCLK31_D14_2)
IBUS_D27: U401.B10 (IO_L35P_GCLK17_0), U501.M7 (IO_L31N_GCLK30_D15_2)
IBUS_D28: U401.D9 (IO_L40N_0), U501.N8 (IO_L29N_GCLK2_2)
IBUS_D29: U401.C10 (IO_L37N_GCLK12_0), U501.L7 (IO_L62N_D6_2)
IBUS_D30: U401.E10 (IO_L37P_GCLK13_0), U501.P8 (IO_L30P_GCLK1_D13_2)
IBUS_D31: U401.C11 (IO_L39P_0), U501.T7 (IO_L32N_GCLK28_2)
INIT: U201.AA33 (INIT), U801.A14 (IO_L65N_SCP2_0)
INTR: U201.AD34 (INTR/LINT0), U801.B16 (IO_L29N_A22_M1A14_1)
ISA5_A0: J901.A31 (BA00), J902.A31 (BA00), R905.2, U909.12 (A0), U1103.8 (A6)
ISA5_A1: J901.A30 (BA01), J902.A30 (BA01), R904.2, U909.11 (A1), U1103.9 (A7)
ISA5_A2: J901.A29 (BA02), J902.A29 (BA02), R903.2, U909.10 (A2), U1103.7 (A5)
ISA5_A3: J901.A28 (BA03), J902.A28 (BA03), U908.11 (Y7), U909.9 (A3)
ISA5_A4: J901.A27 (BA04), J902.A27 (BA04), U908.12 (Y6), U909.8 (A4)
ISA5_A5: J901.A26 (BA05), J902.A26 (BA05), U908.13 (Y5), U909.7 (A5)
ISA5_A6: J901.A25 (BA06), J902.A25 (BA06), U908.14 (Y4), U909.6 (A6)
ISA5_A7: J901.A24 (BA07), J902.A24 (BA07), U908.15 (Y3), U909.5 (A7)
ISA5_A8: J901.A23 (BA08), J902.A23 (BA08), U908.16 (Y2), U909.27 (A8)
ISA5_A9: J901.A22 (BA09), J902.A22 (BA09), U908.17 (Y1), U909.26 (A9)
ISA5_A10: J901.A21 (BA10), J902.A21 (BA10), U908.18 (Y0), U909.23 (A10)
ISA5_A11: J901.A20 (BA11), J902.A20 (BA11), U909.25 (A11), U911.11 (Y7)
ISA5_A12: J901.A19 (BA12), J902.A19 (BA12), U909.4 (A12), U911.12 (Y6)
ISA5_A13: J901.A18 (BA13), J902.A18 (BA13), U909.28 (A13), U911.13 (Y5)
ISA5_A14: J901.A17 (BA14), J902.A17 (BA14), U909.29 (A14), U911.14 (Y4)
ISA5_A15: J901.A16 (BA15), J902.A16 (BA15), U909.3 (A15), U911.15 (Y3)
ISA5_A16: J901.A15 (BA16), J902.A15 (BA16), U909.2 (A16), U911.16 (Y2)
ISA5_A17: J901.A14 (BA17), J902.A14 (BA17), U911.17 (Y1)
ISA5_A18: J901.A13 (BA18), J902.A13 (BA18), U911.18 (Y0)
ISA5_A19: J901.A12 (BA19), J902.A12 (BA19), U912.16 (Y2)
ISA5_D0: J901.A9 (DB0), J902.A9 (DB0), U902.10 (1B5), U907.4 (AD0), U909.13 (D0)
ISA5_D1: J901.A8 (DB1), J902.A8 (DB1), U902.9 (1B4), U907.5 (AD1), U909.14 (D1)
ISA5_D2: J901.A7 (DB2), J902.A7 (DB2), U902.6 (1B3), U907.6 (AD2), U909.15 (D2)
ISA5_D3: J901.A6 (DB3), J902.A6 (DB3), U902.5 (1B2), U907.7 (AD3), U909.17 (D3)
ISA5_D4: J901.A5 (DB4), J902.A5 (DB4), U902.2 (1B1), U907.8 (AD4), U909.18 (D4)
ISA5_D5: J901.A4 (DB5), J902.A4 (DB5), U902.19 (2B3), U907.9 (AD5), U909.19 (D5)
ISA5_D6: J901.A3 (DB6), J902.A3 (DB6), U902.20 (2B4), U907.10 (AD6), U909.20 (D6)
ISA5_D7: J901.A2 (DB7), J902.A2 (DB7), U902.23 (2B5), U907.11 (AD7), U909.21 (D7)
ISA5_D8: J901.C11 (D8), J902.C11 (D8), U902.16 (2B2)
ISA5_D9: J901.C12 (D9), J902.C12 (D9), U902.15 (2B1)
ISA5_D10: J901.C13 (D10), J902.C13 (D10), U904.23 (2B5)
ISA5_D11: J901.C14 (D11), J902.C14 (D11), U904.20 (2B4)
ISA5_D12: J901.C15 (D12), J902.C15 (D12), U904.19 (2B3)
ISA5_D13: J901.C16 (D13), J902.C16 (D13), U904.2 (1B1)
ISA5_D14: J901.C17 (D14), J902.C17 (D14), U904.5 (1B2)
ISA5_D15: J901.C18 (D15), J902.C18 (D15), U904.6 (1B3)
ISA5_IO_READY: J901.A10 (IO_READY), J902.A10 (IO_READY), J1102.27 (IORDY), RN903.3 (R3.1), U910.9 (1B4)
ISA5_IRQ14: J901.D7 (IRQ14), J902.D7 (IRQ14), J1102.31 (INTRQ), RN903.1 (R1.1), U910.19 (2B3)
ISA_A0: U801.P6 (IO_L47P_2), U905.4 (A2)
ISA_A1: U801.N6 (IO_L64N_D9_2), U905.3 (A1)
ISA_A2: U801.P5 (IO_L49N_D4_2), U905.2 (A0)
ISA_A3: U801.N5 (IO_L49P_D3_2), U908.9 (A7)
ISA_A4: U801.M5 (IO_L2P_3), U908.8 (A6)
ISA_A5: U801.N4 (IO_L2N_3), U908.7 (A5)
ISA_A6: U801.M4 (IO_L1P_3), U908.6 (A4)
ISA_A7: U801.L5 (IO_L45N_M3ODT_3), U908.5 (A3)
ISA_A8: U801.M3 (IO_L1N_VREF_3), U908.4 (A2)
ISA_A9: U801.L4 (IO_L45P_M3A3_3), U908.3 (A1)
ISA_A10: U801.L3 (IO_L36P_M3DQ8_3), U908.2 (A0)
ISA_A11: U801.L8 (IO_L62P_D5_2), U911.9 (A7)
ISA_A12: U801.K3 (IO_L42P_GCLK25_TRDY2_M3UDM_3), U911.8 (A6)
ISA_A13: U801.J4 (IO_L42N_GCLK24_M3LDM_3), U911.7 (A5)
ISA_A14: U801.J3 (IO_L38P_M3DQ2_3), U911.6 (A4)
ISA_A15: U801.K5 (IO_L47P_M3A0_3), U911.5 (A3)
ISA_A16: U801.K6 (IO_L47N_M3A1_3), U911.4 (A2)
ISA_A17: U801.J6 (IO_L43P_GCLK23_M3RASN_3), U911.3 (A1)
ISA_A18: U801.H5 (IO_L43N_GCLK22_IRDY2_M3CASN_3), U911.2 (A0)
ISA_A19: U801.H3 (IO_L44N_GCLK20_M3A6_3), U912.4 (A2)
ISA_AEN: U801.K12 (IO_L42P_GCLK7_M1UDM_1), U901.9 (A7)
ISA_ALE: U801.P12 (IO_L12N_D2_MISO3_2), U903.9 (A7)
ISA_CLK: U801.T13 (IO_L51N_M1DQ13_1), U901.5 (A3)
ISA_D0: U801.P2 (IO_L33P_M3DQ12_3), U902.11 (1A5), U1102.9 (A8)
ISA_D1: U801.P1 (IO_L33N_M3DQ13_3), U902.8 (1A4), U1102.7 (A6)
ISA_D2: U801.N3 (IO_L34P_M3UDQS_3), U902.7 (1A3), U1102.5 (A4)
ISA_D3: U801.N1 (IO_L34N_M3UDQSN_3), U902.4 (1A2), U1102.3 (A2)
ISA_D4: U801.M1 (IO_L35N_M3DQ11_3), U902.3 (1A1), U1101.9 (A8)
ISA_D5: U801.J1 (IO_L38N_M3DQ3_3), U902.22 (2A5), U1101.7 (A6)
ISA_D6: U801.K2 (IO_L37P_M3DQ0_3), U902.21 (2A4), U1101.5 (A4)
ISA_D7: U801.K1 (IO_L37N_M3DQ1_3), U902.18 (2A3), U1101.3 (A2)
ISA_D8: U801.L1 (IO_L36N_M3DQ9_3), U902.17 (2A2), U1101.2 (A1)
ISA_D9: U801.M2 (IO_L35P_M3DQ10_3), U902.14 (2A1), U1101.4 (A3)
ISA_D10: U801.R1 (IO_L32N_M3DQ15_3), U904.22 (2A5), U1101.6 (A5)
ISA_D11: U801.R2 (IO_L32P_M3DQ14_3), U904.21 (2A4), U1101.8 (A7)
ISA_D12: U801.T3 (IO_L65N_CSO_B_2), U904.18 (2A3), U1102.2 (A1)
ISA_D13: U801.T5 (IO_L48N_RDWR_B_VREF_2), U904.3 (1A1), U1102.4 (A3)
ISA_D14: U801.T6 (IO_L47N_2), U904.4 (1A2), U1102.6 (A5)
ISA_D15: U801.R7 (IO_L32P_GCLK29_2), U904.7 (1A3), U1102.8 (A7)
ISA_DRQ0: U801.J11 (IO_L40P_GCLK11_M1A5_1), U910.4 (1A2)
ISA_DRQ1: U801.T10 (IO_L3N_MOSI_CSI_B_MISO0_2), U906.17 (2A2)
ISA_DRQ2: U801.R5 (IO_L48P_D7_2), U904.14 (2A1)
ISA_DRQ3: U801.M13 (IO_L74P_AWAKE_1), U906.4 (1A2)
ISA_DRQ5: U801.L14 (IO_L47P_FWE_B_M1DQ0_1), U910.7 (1A3)
ISA_DRQ6: U801.L16 (IO_L47N_LDC_M1DQ1_1), U910.17 (2A2)
ISA_DRQ7: U801.K15 (IO_L44P_A3_M1DQ6_1), U910.14 (2A1)
ISA_IO_READY: U801.K16 (IO_L44N_A2_M1DQ7_1), U910.8 (1A4)
ISA_IRQ2: U801.T4 (IO_L63N_2), U904.17 (2A2)
ISA_IRQ3: U801.P8 (IO_L30P_GCLK1_D13_2), U904.11 (1A5)
ISA_IRQ4: U801.T8 (IO_L30N_GCLK0_USERCCLK_2), U906.22 (2A5)
ISA_IRQ5: U801.R9 (IO_L23P_2), U906.21 (2A4)
ISA_IRQ6: U801.T14 (IO_L51P_M1DQ12_1), U906.3 (1A1)
ISA_IRQ7: U801.T9 (IO_L23N_2), U906.18 (2A3)
ISA_IRQ10: U801.P15 (IO_L48P_HDC_M1DQ8_1), U906.11 (1A5)
ISA_IRQ11: U801.N16 (IO_L45N_A0_M1LDQSN_1), U910.22 (2A5)
ISA_IRQ12: U801.L13 (IO_L53N_VREF_1), U910.3 (1A1)
ISA_IRQ14: U801.M16 (IO_L46N_FOE_B_M1DQ3_1), U910.18 (2A3)
ISA_IRQ15: U801.M15 (IO_L46P_FCS_B_M1DQ2_1), U910.21 (2A4)
ISA_LA17: U801.M10 (IO_L16N_VREF_2), U903.4 (A2)
ISA_LA18: U801.L7 (IO_L62N_D6_2), U905.9 (A7)
ISA_LA19: U801.P7 (IO_L31P_GCLK31_D14_2), U905.6 (A4)
ISA_LA20: U801.M6 (IO_L64P_D8_2), U905.5 (A3)
ISA_LA21: U801.M7 (IO_L31N_GCLK30_D15_2), U905.7 (A5)
ISA_LA22: U801.N8 (IO_L29N_GCLK2_2), U905.8 (A6)
ISA_LA23: U801.L10 (IO_L16P_2), U903.2 (A0)
ISA_RESET: U801.M9 (IO_L29P_GCLK3_2), U903.3 (A1)
ISA_SBHE: U801.T15 (IO_L50N_M1UDQSN_1), U906.7 (1A3)
ISA_SLOT_OSC: R801.2, U912.9 (A7)
ISA_TC: U801.R12 (IO_L52P_M1DQ14_1), U901.3 (A1)
JTAG1_CTRL_TDI: U401.C12 (TDI), U501.E14 (TDO)
JTAG1_TCK: J1104.2, U401.C14 (TCK), U501.C14 (TCK)
JTAG1_TDI: J1104.5, U501.C12 (TDI)
JTAG1_TDO: J1104.4, U401.E14 (TDO)
JTAG1_TMS: J1104.1, U401.A15 (TMS), U501.A15 (TMS)
JTAG2_TCK: J1108.2, U801.C14 (TCK)
JTAG2_TDI: J1108.5, U801.C12 (TDI)
JTAG2_TDO: J1108.4, U801.E14 (TDO)
JTAG2_TMS: J1108.1, U801.A15 (TMS)
KEYBOARD5_CLK: J1101.5 (KB_CLK), RN1101.1 (R1.1), U705.17 (2A2)
KEYBOARD5_DATA: J1101.1 (KB_DATA), RN1101.2 (R2.1), U705.18 (2A3)
KEYBOARD_CLK: U705.16 (2B2), U801.A8 (IO_L33N_0)
KEYBOARD_DATA: U705.19 (2B3), U801.A7 (IO_L6N_0)
MAIN_CLK33: R401.1, U606.1 (CLKIN)
MOUSE5_CLK: J1101.11 (MS_CLK), RN1101.3 (R3.1), U705.22 (2A5)
MOUSE5_DATA: J1101.7 (MS_DATA), RN1101.4 (R4.1), U705.21 (2A4)
MOUSE_CLK: U705.23 (2B5), U801.A6 (IO_L4N_0)
MOUSE_DATA: U705.20 (2B4), U801.B6 (IO_L4P_0)
NMI: U201.AC33 (NMI/LINT1), U801.B14 (IO_L65P_SCP3_0)
unnamed: C1015.1, R1002.2
unnamed: D601.2 (A), R602.2
unnamed: C1001.1, D1001.1 (K), U1001.1 (BST)
unnamed: D1101.2 (A), J1105.1, Q1101.3 (D), R1102.2
unnamed: J201.1, RN203.7 (R2.2), U201.Y33 ([BF0])
unnamed: J201.3, RN203.6 (R3.2), U201.X34 ([BF1])
unnamed: J201.5, RN203.5 (R4.2), U201.W35 ([BF2])
unnamed: J602.A5 (CC1), R611.1
unnamed: J602.B5 (CC2), R612.1
unnamed: J1105.4, R1101.2, R1102.1
unnamed: J1106.3, R1105.2
unnamed: J1107.1, R1103.2
unnamed: J1107.2, R1106.1
unnamed: JP601.1 (A), U604.3 (VO)
unnamed: Q601.1 (G), R606.2
unnamed: Q1101.1 (G), R1108.2
unnamed: R1005.1, SW1001.1
unnamed: R1006.1, SW1001.2
unnamed: R1007.1, SW1001.3
unnamed: R1008.1, SW1001.4
unnamed: R1009.1, SW1001.5
unnamed: RN201.1 (R1.1), U201.N05 (DP7)
unnamed: RN201.2 (R2.1), U201.F02 (DP6)
unnamed: RN201.3 (R3.1), U201.F06 (DP5)
unnamed: RN201.4 (R4.1), U201.C07 (DP4)
unnamed: RN202.1 (R1.1), U201.D18 (DP3)
unnamed: RN202.2 (R2.1), U201.C25 (DP2)
unnamed: RN202.3 (R3.1), U201.D30 (DP1)
unnamed: RN202.4 (R4.1), U201.D36 (DP0)
unnamed: TP204.1, U201.M34 (TCK)
unnamed: TP203.1, U201.N35 (TDI)
unnamed: TP202.1, U201.N33 (TDO)
unnamed: TP201.1, U201.P34 (TMS)
unnamed: TP401.1, U401.B14 (IO_L65P_SCP3_0)
unnamed: R401.2, U401.T3 (IO_L65N_CSO_B_2)
unnamed: TP601.1, U602.15 (GPIO12)
unnamed: R609.1, U602.32 (GPIO21)
unnamed: R605.2, U602.46 (USB_DM)
unnamed: R603.2, U602.47 (USB_DP)
unnamed: C607.1, C608.1, C609.1, U602.23 (DVDD), U602.45 (VREG_VOUT), U602.50 (DVDD)
unnamed: U602.20 (XIN), Y601.3 (OUT)
unnamed: R613.2, R614.1, U603.1 (ADJ)
unnamed: R623.1, U605.5 (1Y2)
unnamed: R624.1, U605.8 (1Y3)
unnamed: R625.1, U605.9 (1Y4)
unnamed: R626.1, U605.20 (2Y1)
unnamed: R629.1, U605.17 (2Y2)
unnamed: R631.1, U605.16 (2Y3)
unnamed: R633.1, U605.12 (2Y4)
unnamed: R627.1, U606.3 (1Y0)
unnamed: R628.1, U606.5 (1Y1)
unnamed: R630.1, U606.7 (1Y2)
unnamed: R632.1, U606.8 (1Y3)
unnamed: R901.1, U901.12 (Y6)
unnamed: R902.1, U903.12 (Y6)
unnamed: R903.1, U905.18 (Y0)
unnamed: R904.1, U905.17 (Y1)
unnamed: R905.1, U905.16 (Y2)
unnamed: U907.2 (X1), Y901.2
unnamed: U907.3 (X2), Y901.1
unnamed: C1107.1, U1104.28 (C1+)
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

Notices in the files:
pentium_test.kicad_pcb:
All rights reserved
